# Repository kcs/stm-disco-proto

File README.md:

# Prototype Shield for STM32F746NG-DISCO

EAGLE schematic and layout files for a simple prototyping shield designed for
the STM32F746NG Discovery board, connecting to the Arduino-like connectors.

The shield matches in width the usual Arduino shields, but it is 8cm long to
match the width of the discovery board. The shield is mostly filled with
prototyping holes, but there is room for an SMD IC (1.27 or 0.65mm pitch)
and some SOT-23 tranzistors.

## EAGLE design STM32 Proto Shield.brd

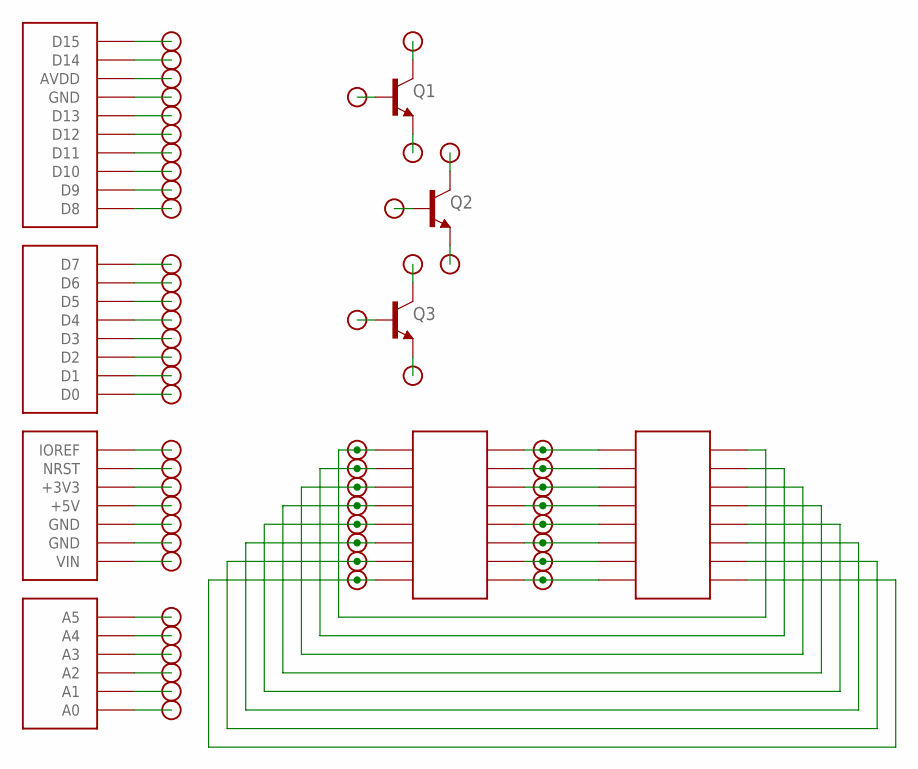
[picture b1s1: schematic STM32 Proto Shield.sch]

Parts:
J1: DISCO_SHIELD_BARE; DISCO_SHIELAD_BARE
Q1, Q2, Q3: BC817-40SMD; SOT23-BEC
U$1, U$2, U$3, U$4, U$5, U$6, U$7, U$8, U$9, U$10, U$11, U$12, U$13, U$14, U$15, U$16, U$17, U$18, U$19, U$20, U$21, U$22, U$23, U$24, U$25, U$26, U$27, U$28, U$29, U$30, U$31, U$32, U$33, U$34, U$35, U$36, U$37, U$38, U$39, U$40, U$42, U$43, U$44, U$45, U$46, U$47, U$48, U$49, U$50, U$51, U$52, U$53, U$54, U$55, U$56, U$57: SOLDER_PAD; 1_08X19
U$41: GENERIC_SMD_16; 16_TSOP_LONG
U$58: GENERIC_SMD_16SOIC_LONG; 16_SOIC_LONG

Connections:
unnamed: U$41.P$1, U$42.P$1, U$58.P$16
unnamed: U$41.P$2, U$43.P$1, U$58.P$15
unnamed: U$41.P$3, U$44.P$1, U$58.P$14
unnamed: U$41.P$16, U$57.P$1, U$58.P$1
unnamed: U$41.P$15, U$56.P$1, U$58.P$2
unnamed: U$41.P$14, U$55.P$1, U$58.P$3
unnamed: U$41.P$13, U$54.P$1, U$58.P$4
unnamed: U$41.P$12, U$53.P$1, U$58.P$5
unnamed: U$41.P$11, U$52.P$1, U$58.P$6
unnamed: U$41.P$10, U$51.P$1, U$58.P$7
unnamed: U$41.P$9, U$50.P$1, U$58.P$8
unnamed: U$41.P$4, U$45.P$1, U$58.P$13
unnamed: U$41.P$5, U$46.P$1, U$58.P$12
unnamed: U$41.P$6, U$47.P$1, U$58.P$11
unnamed: U$41.P$7, U$49.P$1, U$58.P$10
unnamed: J1.D15, U$1.P$1
unnamed: J1.D14, U$2.P$1
unnamed: J1.AVDD, U$3.P$1
unnamed: J1.GND_D (GND), U$4.P$1
unnamed: J1.D13, U$5.P$1
unnamed: J1.D12, U$6.P$1
unnamed: J1.D11, U$7.P$1
unnamed: J1.D10, U$8.P$1
unnamed: J1.D9, U$9.P$1
unnamed: J1.D8, U$10.P$1
unnamed: J1.D7, U$11.P$1
unnamed: J1.D6, U$12.P$1
unnamed: J1.D5, U$13.P$1
unnamed: J1.D4, U$14.P$1
unnamed: J1.D3, U$15.P$1
unnamed: J1.D2, U$16.P$1
unnamed: J1.D1, U$17.P$1
unnamed: J1.D0, U$18.P$1
unnamed: J1.IOREF, U$19.P$1
unnamed: J1.RST (NRST), U$20.P$1
unnamed: J1.3V3 (+3V3), U$21.P$1
unnamed: J1.5V (+5V), U$22.P$1
unnamed: J1.GND@2 (GND), U$23.P$1
unnamed: J1.GND@1 (GND), U$24.P$1
unnamed: J1.VIN, U$25.P$1
unnamed: J1.A5, U$26.P$1
unnamed: J1.A4, U$27.P$1
unnamed: J1.A3, U$28.P$1
unnamed: J1.A2, U$29.P$1
unnamed: J1.A1, U$30.P$1
unnamed: J1.A0, U$31.P$1
unnamed: Q1.C, U$32.P$1
unnamed: Q1.B, U$33.P$1
unnamed: Q1.E, U$34.P$1
unnamed: Q2.C, U$35.P$1
unnamed: Q2.B, U$37.P$1
unnamed: Q2.E, U$36.P$1
unnamed: Q3.C, U$38.P$1
unnamed: Q3.B, U$40.P$1
unnamed: Q3.E, U$39.P$1
unnamed: U$41.P$8, U$48.P$1, U$58.P$9

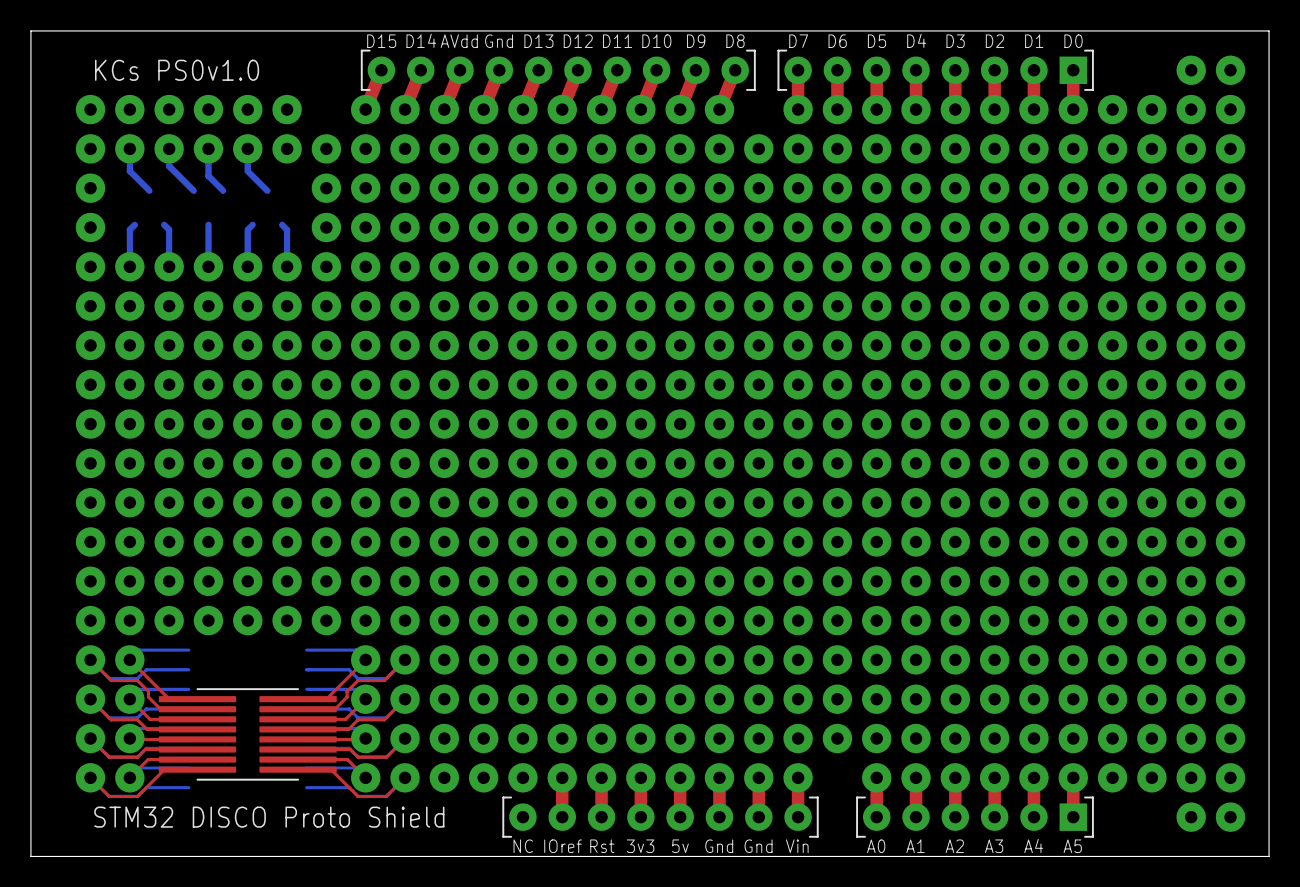
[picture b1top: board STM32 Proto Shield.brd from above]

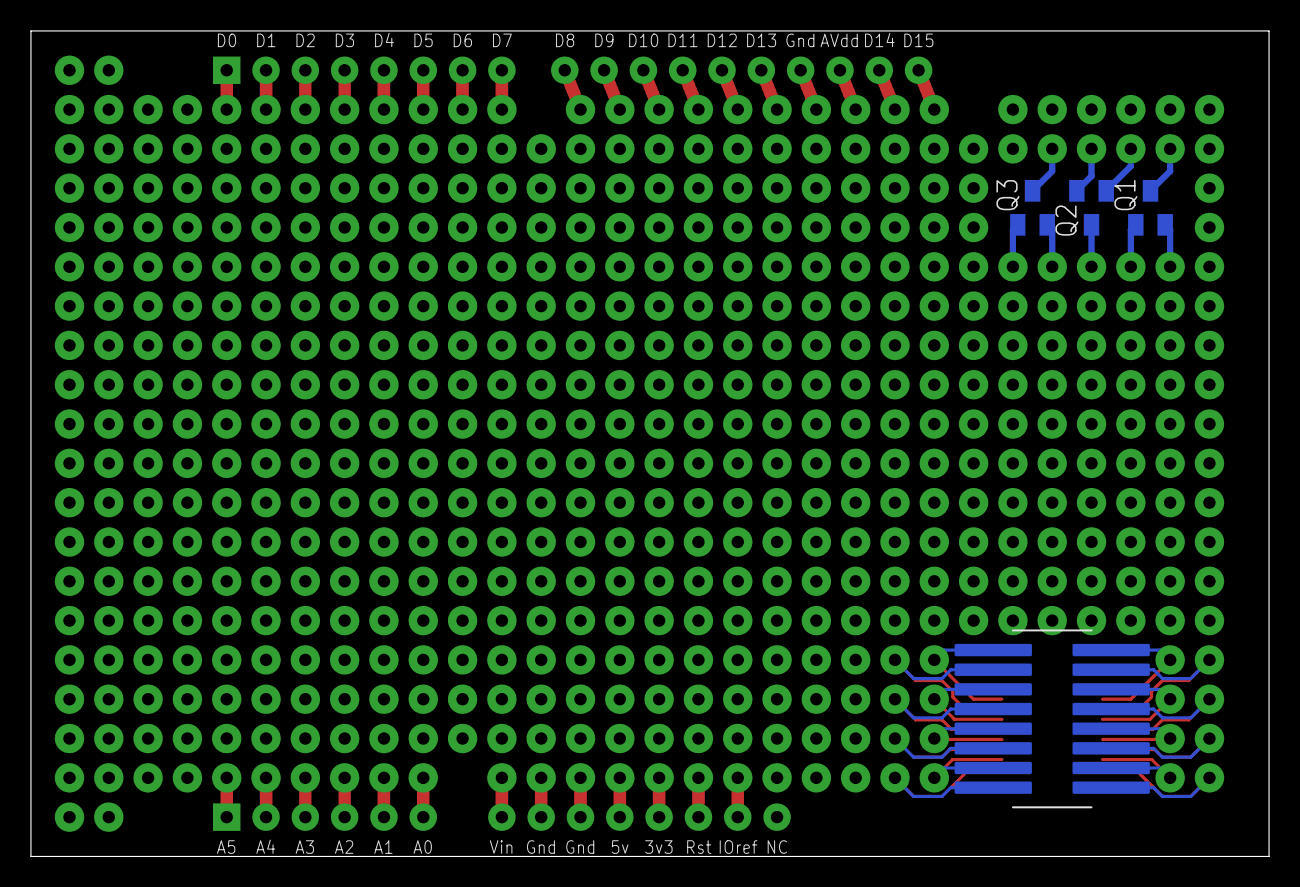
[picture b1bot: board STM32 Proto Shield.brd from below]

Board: 2 copper layers, 80.0 x 53.3 mm, 62 parts (4 on the bottom side), 56 nets.

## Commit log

2020-12-24 Initial commit
    v1.0 of the board
